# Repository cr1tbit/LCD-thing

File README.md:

This repo is so messy, i'm sorry i'm gonna fix it one day

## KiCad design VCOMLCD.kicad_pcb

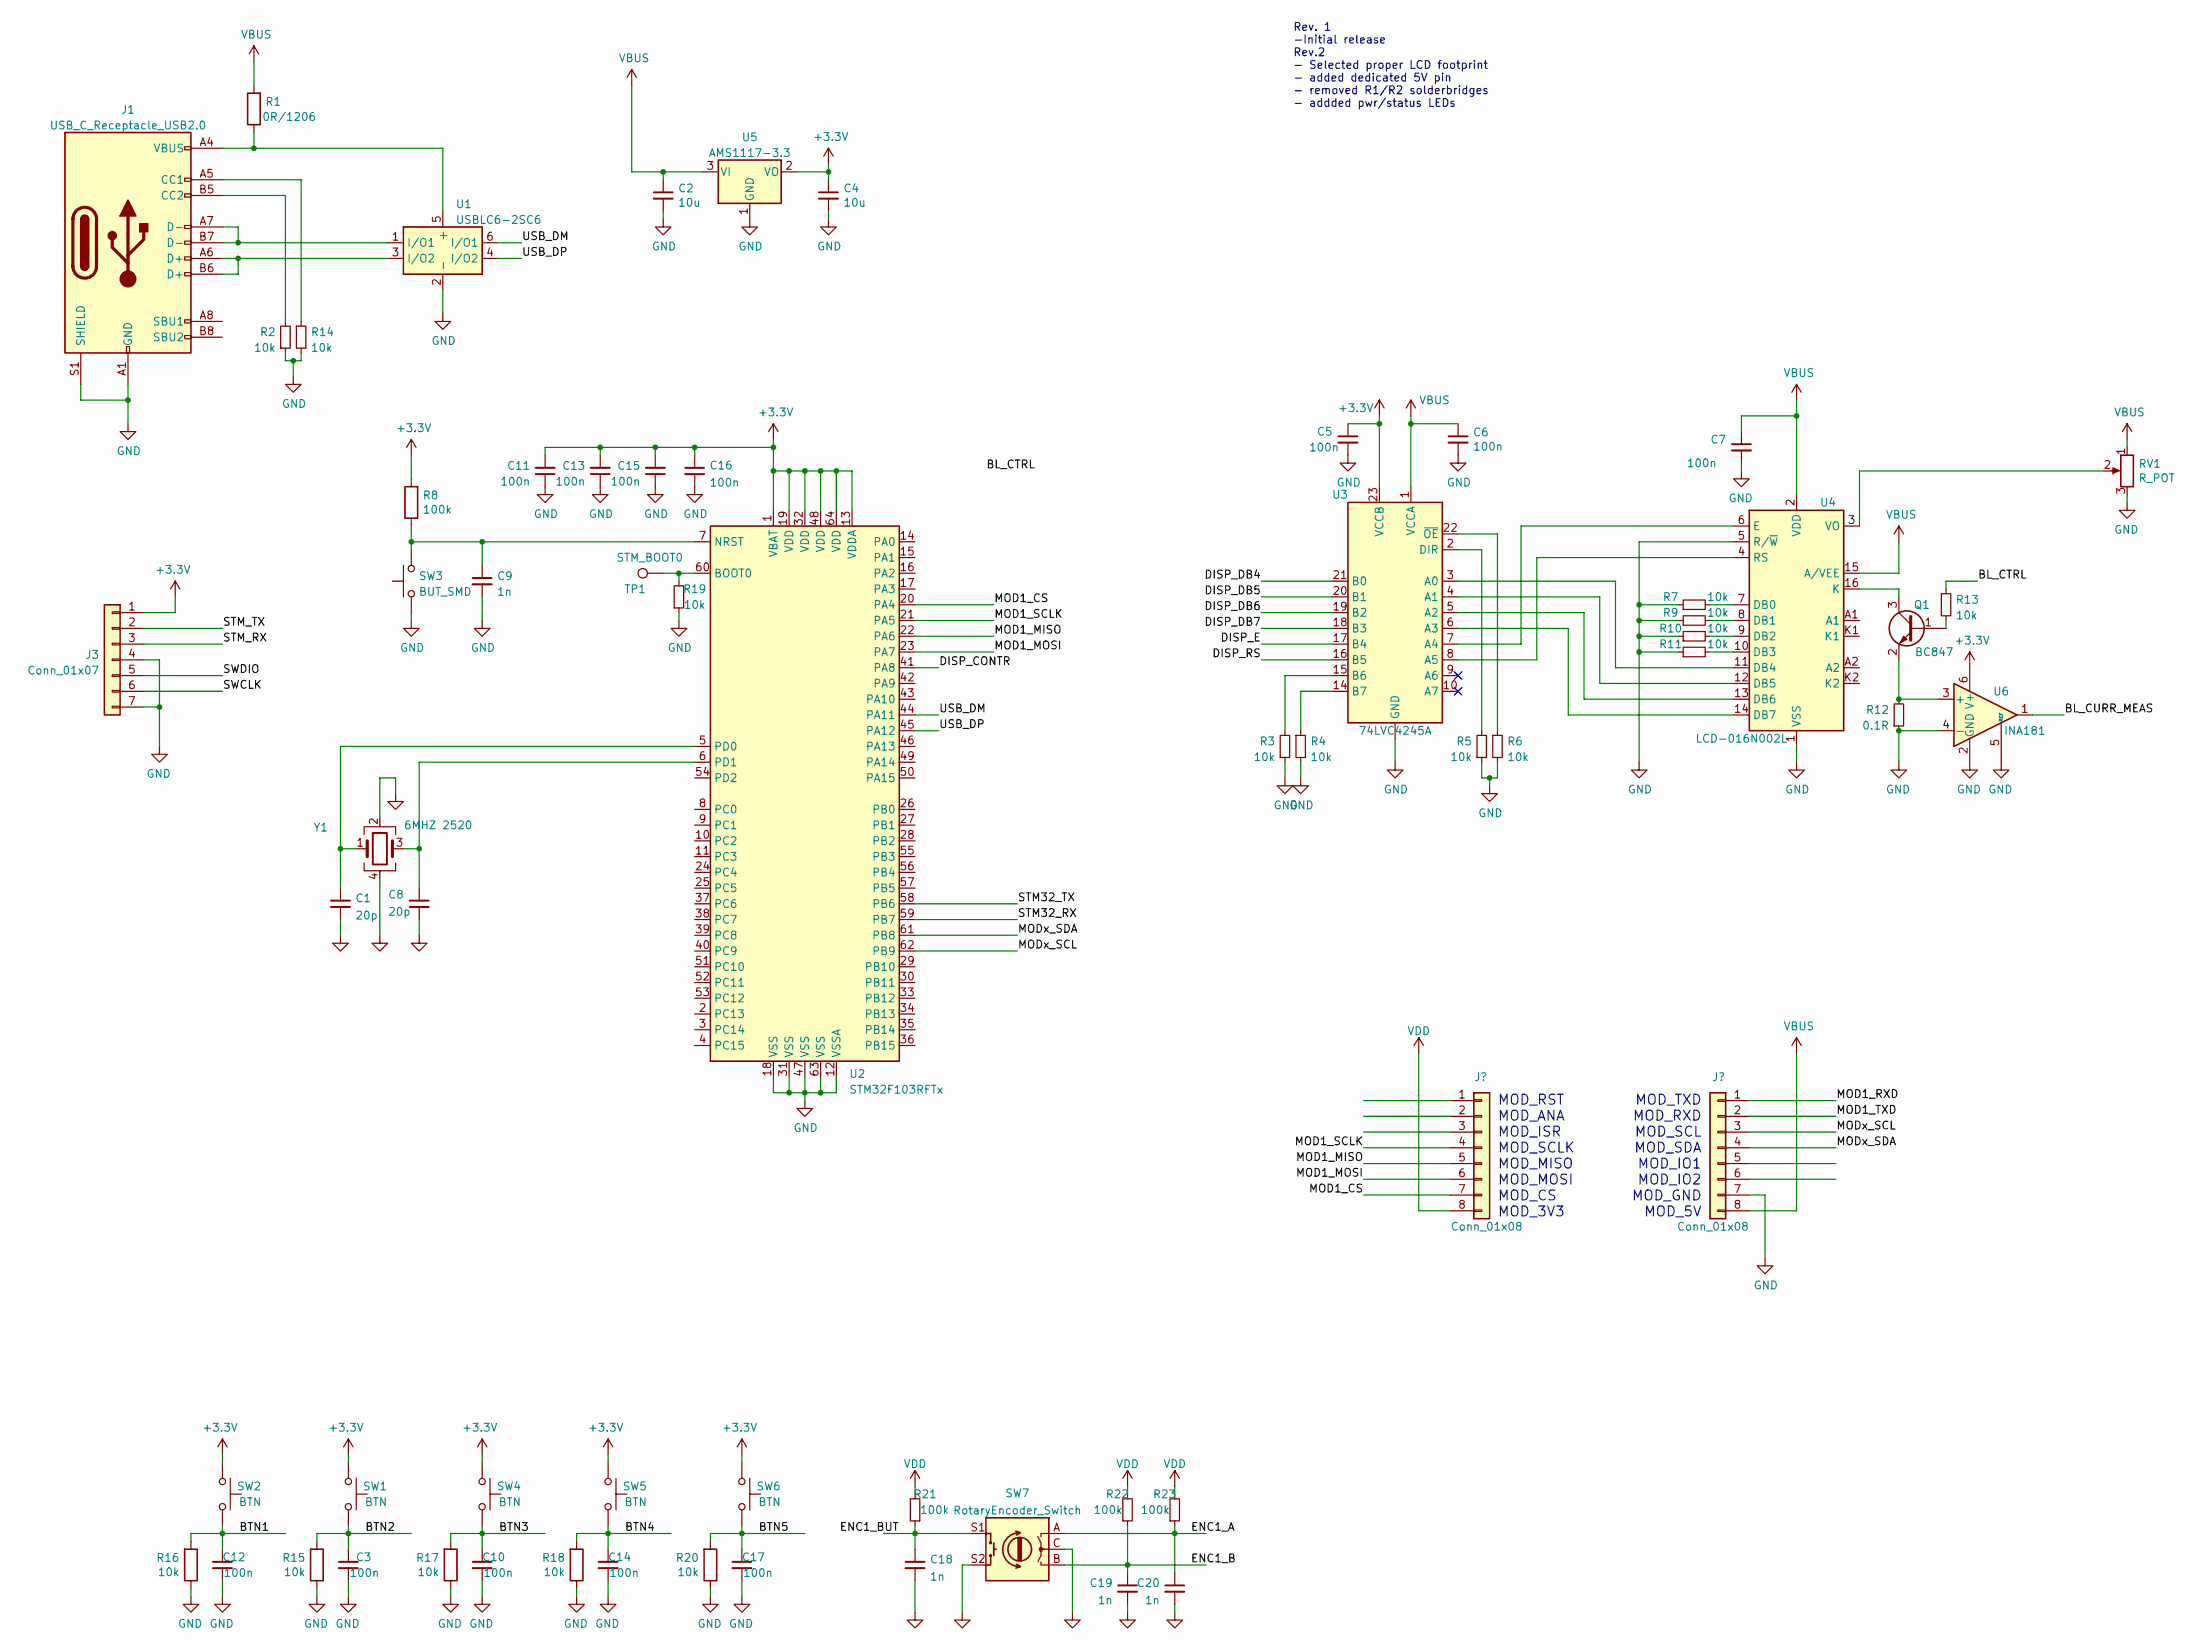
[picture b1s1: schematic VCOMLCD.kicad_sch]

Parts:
C1, C8: 20p; C_0402_1005Metric
C2, C4: 10u; C_0402_1005Metric
C3, C5, C6, C7, C10, C11, C12, C13, C14, C15, C16, C17: 100n; C_0402_1005Metric
C9, C18, C19, C20: 1n; C_0402_1005Metric
J1: USB_C_Receptacle_USB2.0; USB_C_Receptacle_GCT_USB4085
J3: Conn_01x07; PinHeader_1x07_P2.54mm_Vertical
Q1: BC847; SOT-23
R1: 0R/1206; R_1206_3216Metric_Pad1.30x1.75mm_HandSolder
R2, R3, R4, R5, R6, R7, R9, R10, R11, R13, R14, R15, R16, R17, R18, R19, R20: 10k; R_0402_1005Metric
R8, R21, R22, R23: 100k; R_0402_1005Metric
R12: 0.1R; R_1206_3216Metric_Pad1.30x1.75mm_HandSolder
RV1: R_POT; Potentiometer_Vishay_TS53YJ_Vertical
SW1, SW2, SW4, SW5, SW6: BTN; SW_Cherry_MX_1.00u_PCB
SW3: BUT_SMD; Panasonic_EVQPUM_EVQPUD
SW7: RotaryEncoder_Switch; RotaryEncoder_Alps_EC12E-Switch_Vertical_H20mm_CircularMoun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
TP1: STM_BOOT0; TestPoint_Pad_D1.0mm
U1: USBLC6-2SC6; SOT-23-6
U2: STM32F103RFTx; LQFP-64_10x10mm_P0.5mm
U3: 74LVC4245A; SOIC-24W_7.5x15.4mm_P1.27mm
U4: LCD-016N002L
U5: AMS1117-3.3; SOT-223-3_TabPin2
U6: INA181; SOT-23-6
Y1: 6MHZ 2520; Crystal_SMD_2520-4Pin_2.5x2.0mm

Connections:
+3V3: C4.1, C5.1, C11.2, C13.2, C15.2, C16.1, J3.1, R8.2, SW1.2, SW2.2, SW4.2, SW5.2, SW6.2, U2.1 (VBAT), U2.13 (VDDA), U2.19 (VDD), U2.32 (VDD), U2.48 (VDD), U2.64 (VDD), U3.23 (VCCB), U3.24 (VCCB), U5.2 (VO), U6.6 (V+)
/BL_CTRL: R13.1
/BL_CURR_MEAS: U6.1
/BTN1: C12.1, R16.2, SW2.1
/BTN2: C3.1, R15.2, SW1.1
/BTN3: C10.1, R17.2, SW4.1
/BTN4: C14.1, R18.2, SW5.1
/BTN5: C17.1, R20.2, SW6.1
/DISP_CONTR: U2.41 (PA8)
/DISP_DB4: U3.21 (B0)
/DISP_DB5: U3.20 (B1)
/DISP_DB6: U3.19 (B2)
/DISP_DB7: U3.18 (B3)
/DISP_E: U3.17 (B4)
/DISP_RS: U3.16 (B5)
/ENC1_A: C20.1, R23.1, SW7.A
/ENC1_B: C19.1, R22.1, SW7.B
/ENC1_BUT: C18.1, R21.1, SW7.S1
/EXT_CLK: U2.21 (PA5)
/EXT_CS: U2.20 (PA4)
/EXT_MISO: U2.22 (PA6)
/EXT_MOSI: U2.23 (PA7)
/EXT_SCL: U2.62 (PB9)
/EXT_SDA: U2.61 (PB8)
/STM32_RX: U2.59 (PB7)
/STM32_TX: U2.58 (PB6)
/STM_RX: J3.3
/STM_TX: J3.2
/SWCLK: J3.6
/SWDIO: J3.5
/USB_DM: U1.6 (I/O1), U2.44 (PA11)
/USB_DP: U1.4 (I/O2), U2.45 (PA12)
GND: C1.2, C2.2, C3.2, C4.2, C5.2, C6.2, C7.2, C8.2, C9.2, C10.2, C11.1, C12.2, C13.1, C14.2, C15.1, C16.2, C17.2, C18.2, C19.2, C20.2, J1.A1 (GND), J1.A12 (GND), J1.B1 (GND), J1.B12 (GND), J1.S1 (SHIELD), J3.4, J3.7, R2.1, R3.1, R4.2, R5.1, R6.2, R7.1, R9.1, R10.1, R11.1, R12.1, R14.2, R15.1, R16.1, R17.1, R18.1, R19.1, R20.1, RV1.3, SW3.1, SW7.C, SW7.S2, U1.2 (-), U2.12 (VSSA), U2.18 (VSS), U2.31 (VSS), U2.47 (VSS), U2.63 (VSS), U3.11 (GND), U3.12 (GND), U3.13 (GND), U4.1 (VSS), U4.5 (R/~W), U5.1 (GND), U6.2 (GND), U6.4 (-), U6.5 (REF), Y1.2, Y1.4; also elsewhere on the board
unnamed: J1.A4 (VBUS), J1.A9 (VBUS), J1.B4 (VBUS), J1.B9 (VBUS), R1.1, U1.5 (+)
unnamed: J1.A5 (CC1), R14.1
unnamed: J1.A6 (D+), J1.B6 (D+), U1.3 (I/O2)
unnamed: J1.A7 (D-), J1.B7 (D-), U1.1 (I/O1)
unnamed: J1.B5 (CC2), R2.2
unnamed: Q1.1 (B), R13.2
unnamed: Q1.2 (E), R12.2, U6.3 (+)
unnamed: Q1.3 (C), U4.16 (K)
unnamed: RV1.2, U4.3 (VO)
unnamed: C1.1, U2.5 (PD0), Y1.1
unnamed: C8.1, U2.6 (PD1), Y1.3
unnamed: C9.1, R8.1, SW3.2, U2.7 (NRST)
unnamed: R19.2, TP1.1, U2.60 (BOOT0)
unnamed: R5.2, U3.2 (DIR)
unnamed: U3.3 (A0), U4.11 (DB4)
unnamed: U3.4 (A1), U4.12 (DB5)
unnamed: U3.5 (A2), U4.13 (DB6)
unnamed: U3.6 (A3), U4.14 (DB7)
unnamed: U3.7 (A4), U4.6 (E)
unnamed: U3.8 (A5), U4.4 (RS)
unnamed: R4.1, U3.14 (B7)
unnamed: R3.2, U3.15 (B6)
unnamed: R6.1, U3.22 (~OE)
unnamed: R7.2, U4.7 (DB0)
unnamed: R9.2, U4.8 (DB1)
unnamed: R10.2, U4.9 (DB2)
unnamed: R11.2, U4.10 (DB3)
VBUS: C2.1, C6.1, C7.1, R1.2, RV1.1, U3.1 (VCCA), U4.2 (VDD), U4.15 (A/VEE), U5.3 (VI)
VDD: R21.2, R22.2, R23.2; also elsewhere on the board

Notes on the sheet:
MOD_RST MOD_ANA MOD_ISR MOD_SCLK MOD_MISO MOD_MOSI MOD_CS MOD_3V3
MOD_TXD MOD_RXD MOD_SCL MOD_SDA MOD_IO1 MOD_IO2 MOD_GND MOD_5V
Rev. 1 -Initial release Rev.2 - Selected proper LCD footprint - added dedicated 5V pin - removed R1/R2 solderbridges - addded pwr/status LEDs

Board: 2 copper layers, 67 parts (7 on the bottom side), 44 nets, no tracks yet.

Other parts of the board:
J2: EXT_MOD_CONN; PinSocket_2x05_P2.54mm_Vertical
Q2: AO3401A; SOT-23
Q3: BC847; SOT-23
R24: 10k; R_0402_1005Metric
R25: 3k; R_0402_1005Metric

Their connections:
+5V: Q2.2 (S), R24.2
GND: J2.3, J2.7, Q3.2 (E); also elsewhere on the board
unnamed: Q2.1 (G), Q3.3 (C), R24.1
unnamed: Q3.1 (B), R25.2
VDD: J2.4, J2.8; also elsewhere on the board

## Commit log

2019-05-31 rev1 commit
2019-08-12 final rev1 files
2020-05-11 pre-fabrication commit
2020-07-29 adding board bringup tests
2020-08-08 oh darn, how old is this repo
2022-04-08 repo cleanup i guess
2022-04-08 adding schematic
2022-04-28 adding POC firmware
2022-06-02 yeah
2022-08-09 work on new STM version - basic schematic and some of pcb
2022-08-11 WIP commit
